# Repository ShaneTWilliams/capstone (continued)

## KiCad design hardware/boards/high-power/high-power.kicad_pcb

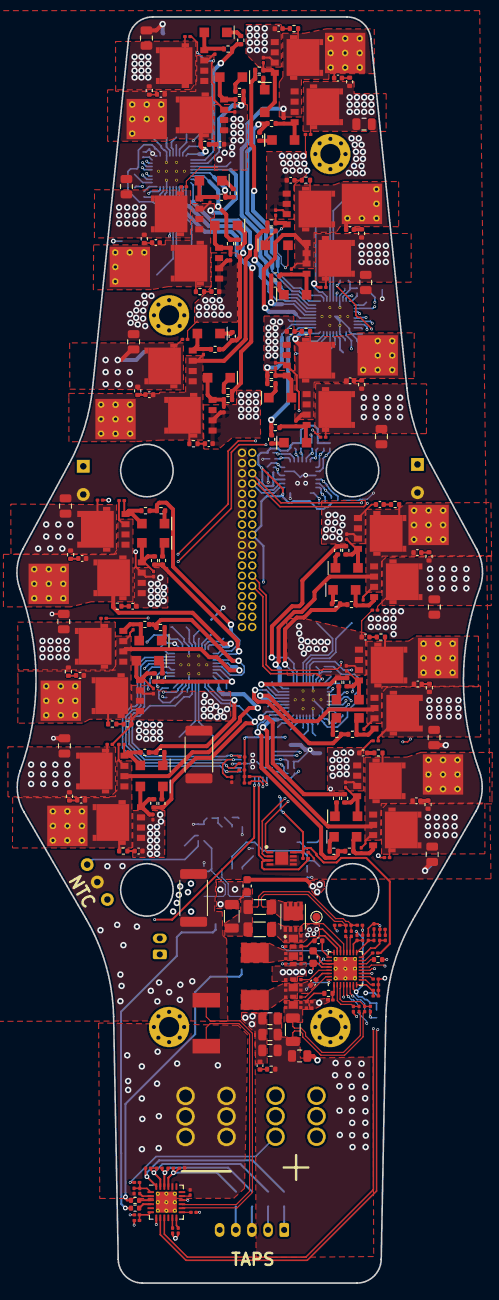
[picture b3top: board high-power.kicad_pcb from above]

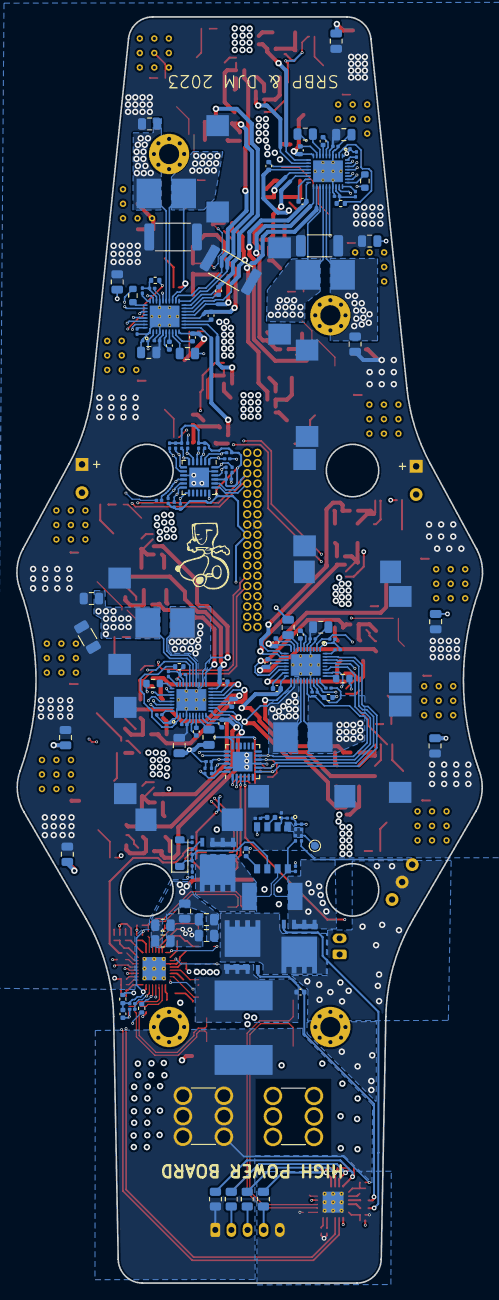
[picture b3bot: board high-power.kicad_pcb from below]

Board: 4 copper layers, 57.7 x 157.0 mm, 435 parts (150 on the bottom side), 262 nets.

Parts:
C201, C208, C209: 0.47uF; C_0201_0603Metric
C202, C425, C427, C428: 0.1uF; C_0201_0603Metric
C203, C204, C205, C206, C210: 0.01uF; C_0201_0603Metric
C207: 0.1uF; C_0402_1005Metric
C401, C413: 1uF; C_0402_1005Metric
C402, C404, C406, C408, C418, C420, C421, C423, C424: 10uF; C_0805_2012Metric
C403: 33pF; C_0201_0603Metric
C405: 1800pF; C_0201_0603Metric
C407: 680pF; C_0201_0603Metric
C409, C412: 33nF; C_0201_0603Metric
C410: 15pF; C_0201_0603Metric
C411: 1nF; C_0201_0603Metric
C414: 10nF; C_0201_0603Metric
C415: 470nF; C_0201_0603Metric
C416, C417: 47nF; C_0402_1005Metric
C419: 3.3uF; C_0603_1608Metric
C422, C426: 100pF; C_0201_0603Metric
C429: 10uF; C_0603_1608Metric
C501, C502, C706, C806, C906, C1006: 0.1u; C_0201_0603Metric
C503: 6.2n; C_0402_1005Metric
C504: 10n; C_0201_0603Metric
C505, C506, C508, C509, C511, C512, C513, C514, C515, C516, C704, C705, C804, C805, C904, C905, C1004, C1005: 10u; C_0805_2012Metric
C507, C510: 220u; CP_Radial_D8.0mm_P3.50mm
C601, C602, C1101: 100n; C_0201_0603Metric
C701, C702, C703, C801, C802, C803, C901, C902, C903, C1001, C1002, C1003: 1u; C_0201_0603Metric
C707, C807, C907, C1007: 470n; C_0402_1005Metric
C708, C709, C710, C808, C809, C810, C908, C909, C910, C1008, C1009, C1010: 1u; C_0402_1005Metric
C711, C712, C715, C716, C719, C720, C811, C812, C815, C816, C819, C820, C911, C912, C915, C916, C919, C920, C1011, C1012, C1015, C1016, C1019, C1020: 3900p; C_0402_1005Metric
C713, C717, C721, C813, C817, C821, C913, C917, C921, C1013, C1017, C1021: 0.01u; C_0201_0603Metric
C714, C718, C722, C814, C818, C822, C914, C918, C922, C1014, C1018, C1022: 4.7u; C_0805_2012Metric
D501: MMSZ5248B; D_SOD-123
D502: SML-P11UTT86R; LED_0402_1005Metric
D701, D702, D703, D704, D705, D706, D801, D802, D803, D804, D805, D806, D901, D902, D903, D904, D905, D906, D1001, D1002, D1003, D1004, D1005, D1006: PMEG4030ER,115; SOD123W
F201: 3-139-122 50A Fuse; 3-139-124
H101, H102, H103, H104: MountingHole; MountingHole_2.5mm_Pad_Via
J101: Conn_02x18_Top_Bottom; 20021311-00036T4LF
J201, J202: Screw_Terminal_01x01; 7461057
J203: Cell Taps; JST_PH_S5B-PH-K_1x05_P2.00mm_Horizontal
J204: 10k NTC Thermistor; JST_PH_S2B-PH-K_1x02_P2.00mm_Horizontal
J601, J701, J801, J901: C; MotorPad
J602, J702, J802, J902: B; MotorPad
J603, J703, J803, J903: A; MotorPad
L401: 2.2u; IHLP2525EZER2R2M01
Q101, Q201, Q202: BSC005N03LS5
Q401, Q402, Q403, Q404: DMN3020UFDF-7
Q405: DMP3013SFV; DMP3013SFV7
Q701, Q702, Q703, Q704, Q705, Q706, Q801, Q802, Q803, Q804, Q805, Q806, Q901, Q902, Q903, Q904, Q905, Q906, Q1001, Q1002, Q1003, Q1004, Q1005, Q1006: NTMFS5C426NT1G
R100, R101, R103, R104: 0; R_2512_6332Metric
R102: 0; R_2010_5025Metric
R105, R107, R108, R109, R110, R111, R112, R113, R114, R115, R116: 0; 5104TR
R106: 0; R_1206_3216Metric
R201, R420, R423: 10R; R_0201_0603Metric
R202, R203, R204: 27R 1/2W; R_0805_2012Metric
R205: 51R 1/2W; R_0805_2012Metric
R206, R211, R507: 1k; R_0201_0603Metric
R207, R504: 1m; EBWM2512F1L00S9
R208, R209: 100R; R_0402_1005Metric
R210, R403, R410, R412, R415, R601, R602, R603, R703, R704, R705, R712, R713, R720, R721, R729, R730, R803, R804, R805, R812, R813, R820, R821, R829, R830, R903, R904, R905, R912, R913, R920, R921, R929, R930, R1003, R1004, R1005, R1012, R1013, R1020, R1021, R1029, R1030, R1101, R1102: 10k; R_0201_0603Metric
R401: 2.2R; R_0402_1005Metric
R402: 40.2k; R_0201_0603Metric
R404, R406: 4.99R; R_0201_0603Metric
R405, R421: 10m; R_1206_3216Metric
R407: 10R; R_0402_1005Metric
R408: 76.8k; R_0201_0603Metric
R409, R417, R502, R508: 100k; R_0201_0603Metric
R411: 1R; R_0402_1005Metric
R413, R414: 0R; R_0402_1005Metric
R416: 30k; R_0201_0603Metric
R418: 300k; R_0201_0603Metric
R419, R424: 0R; R_1206_3216Metric
R422: 137k; R_0201_0603Metric
R501, R506: 100; R_0201_0603Metric
R503, R509: 10.6k; R_0201_0603Metric
R505: 10; R_0201_0603Metric
R510: 13k; R_0201_0603Metric
R701, R702, R801, R802, R901, R902, R1001, R1002: 5.1k; R_0201_0603Metric
R706, R806, R906, R1006: 0; R_0402_1005Metric
R707, R807, R907, R1007: 0R; R_0603_1608Metric
R708, R709, R710, R711, R714, R715, R716, R719, R722, R723, R725, R728, R808, R809, R810, R811, R814, R815, R816, R819, R822, R823, R825, R828, R908, R909, R910, R911, R914, R915, R916, R919, R922, R923, R925, R928, R1008, R1009, R1010, R1011, R1014, R1015, R1016, R1019, R1022, R1023, R1025, R1028: 15; R_0402_1005Metric
R717, R718, R726, R727, R731, R732, R817, R818, R826, R827, R831, R832, R917, R918, R926, R927, R931, R932, R1017, R1018, R1026, R1027, R1031, R1032: 1.50; R_0402_1005Metric
R724, R824, R924, R1024: 2m; PA2512FKF7T0R002E
SW501: SW_SPDT; EG1270
TP407: TestPoint; TestPoint_Pad_D1.0mm
TP501: ON; TestPoint_Pad_D1.0mm
U201: MAX17320G20+T; QFN-24-1EP_4x4mm_P0.5mm_EP2.6x2.6mm_ThermalVias
U401: BQ25703ARSNT; QFN-32-1EP_4x4mm_P0.4mm_EP2.9x2.9mm_ThermalVias
U501: LT1641-1; LT1641-1CS8TRPBF
U601, U1101: TCA9539RTWR; WQFN-24-1EP_4x4mm_P0.5mm_EP2.45x2.45mm
U602: LM75BTP,147
U701, U801, U901, U1001: MCT8329A

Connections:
+3V3: C601.1, C602.1, C1101.1, J101.27, R410.2, R412.1, R415.2, R602.1, R603.1, R701.1, R703.1, R704.1, R801.1, R803.1, R804.1, R901.1, R903.1, R904.1, R1001.1, R1003.1, R1004.1, R1102.1, U601.21 (VCC), U602.8 (VCC), U1101.18 (A0), U1101.21 (VCC)
+BATT: C505.1, C506.1, C507.1, C508.1, C509.1, C510.1, C511.1, C512.1, C513.1, C514.1, C515.1, C516.1, C704.2, C706.2, C713.2, C714.2, C717.2, C718.2, C721.2, C722.2, C804.2, C806.2, C813.2, C814.2, C817.2, C818.2, C821.2, C822.2, C904.2, C906.2, C913.2, C914.2, C917.2, C918.2, C921.2, C922.2, C1004.2, C1006.2, C1013.2, C1014.2, C1017.2, C1018.2, C1021.2, C1022.2, J101.8, Q101.3 (S), Q701.3 (D), Q703.3 (D), Q705.3 (D), Q801.3 (D), Q803.3 (D), Q805.3 (D), Q901.3 (D), Q903.3 (D), Q905.3 (D), Q1001.3 (D), Q1003.3 (D), Q1005.3 (D), R100.1, R100.2, R101.1, R101.2, R102.1, R102.2, R105.1, R105.2, R106.1, R106.2, R107.1, R107.2, R108.1, R108.2, R109.1, R109.2, R110.1, R110.2, R111.1, R111.2, R112.1, R112.2, R113.1, R113.2, R114.1, R114.2, R115.1, R115.2, R116.1, R116.2, R506.2, R508.1, R510.1, R717.1, R726.1, R731.1, R817.1, R826.1, R831.1, R917.1, R926.1, R931.1, R1017.1, R1026.1, R1031.1, U701.5 (PVDD), U801.5 (PVDD), U901.5 (PVDD), U1001.5 (PVDD)
/MTR_FL_CS: J101.19, U701.33 (DACOUT/SOx/SPEED_ANA)
/MTR_FL_SPEED: J101.20, U701.27 (SPEED/WAKE)
/MTR_FR_CS: J101.26, U801.33 (DACOUT/SOx/SPEED_ANA)
/MTR_FR_SPEED: J101.25, U801.27 (SPEED/WAKE)
/MTR_RL_CS_CONN: J101.13, U901.33 (DACOUT/SOx/SPEED_ANA)
/MTR_RL_SPD_CONN: J101.12, U901.27 (SPEED/WAKE)
/MTR_RR_CS: J101.31, U1001.33 (DACOUT/SOx/SPEED_ANA)
/MTR_RR_SPEED: J101.32, U1001.27 (SPEED/WAKE)
/Motors/ESC_FL/BRAKE: R703.2, U601.3 (P02), U701.34 (BRAKE)
/Motors/ESC_FL/DIR: R705.1, U601.1 (P00), U701.31 (DIR)
/Motors/ESC_FL/DRVOFF: R704.2, U601.2 (P01), U701.24 (DRVOFF)
/Motors/ESC_FL/FG: R702.2, U701.28 (FG)
/Motors/ESC_FL/nFAULT: R701.2, U601.4 (P03), U701.35 (nFAULT)
/Motors/ESC_FR/BRAKE: R803.2, U601.7 (P06), U801.34 (BRAKE)
/Motors/ESC_FR/DIR: R805.1, U601.5 (P04), U801.31 (DIR)
/Motors/ESC_FR/DRVOFF: R804.2, U601.6 (P05), U801.24 (DRVOFF)
/Motors/ESC_FR/FG: R802.2, U801.28 (FG)
/Motors/ESC_FR/nFAULT: R801.2, U601.8 (P07), U801.35 (nFAULT)
/Motors/ESC_RL/FG: R902.2, U901.28 (FG)
/Motors/ESC_RL_BRAKE: R903.2, U901.34 (BRAKE), U1101.8 (P07)
/Motors/ESC_RL_DIR: R905.1, U901.31 (DIR), U1101.10
/Motors/ESC_RL_DRVOFF: R904.2, U901.24 (DRVOFF), U1101.11
/Motors/ESC_RL_nFAULT: R901.2, U901.35 (nFAULT), U1101.7 (P06)
/Motors/ESC_RR/BRAKE: R1003.2, U601.12, U1001.34 (BRAKE)
/Motors/ESC_RR/DIR: R1005.1, U601.10, U1001.31 (DIR)
/Motors/ESC_RR/DRVOFF: R1004.2, U601.11, U1001.24 (DRVOFF)
/Motors/ESC_RR/FG: R1002.2, U1001.28 (FG)
/Motors/ESC_RR/nFAULT: R1001.2, U601.13, U1001.35 (nFAULT)
/Motors/~MTR_TMP_OS: R603.2, U602.3 (OS), U1101.3 (P02)
/Power & Charging/BMS/CELL1: J203.4, R205.1
/Power & Charging/BMS/CELL2: J203.3, R204.1
/Power & Charging/BMS/CELL3: J203.2, R203.1
/Power & Charging/BMS/CELL4: F201.1, J202.1, J203.1, R201.1, R202.1
/Power & Charging/BMS_ALRT: U201.7 (ALRT), U1101.4 (P03)
/Power & Charging/CC_CHRG_OK: R412.2, U401.4 (CHRG_OK), U1101.2 (P01)
/Power & Charging/Charge Controller/ILIM_HIZ: R408.2, R409.1, U401.6 (ILIM_HIZ)
/Power & Charging/Charge Controller/REGN: C419.1, R407.1, U401.28 (REGN)
/Power & Charging/Charge Controller/VDDA: C413.1, R407.2, R408.1, R417.1, U401.7 (VDDA)
/Power & Charging/Hotswap/BATT_GOOD: D502.2 (A), R510.2
/Power & Charging/Hotswap/BATT_RAW: C502.1, Q202.3 (S), R211.1, R424.1, R502.1, R504.2, U501.8 (Vcc)
/Power & Charging/Hotswap/SENSE: Q101.1 (D), R504.1, U501.7 (Sense)
/Power & Charging/~CC_PROCHOT: R410.1, U401.11 (~PROCHOT), U1101.1 (P00)
/SCL: J101.22, U201.8 (SCL), U401.13 (SCL), U601.19 (SCL), U602.2 (SCL), U701.30 (SCL), U801.30 (SCL), U901.30 (SCL), U1001.30 (SCL), U1101.19 (SCL)
/SDA: J101.21, R707.1, R807.1, R907.1, R1007.1, U201.9 (SDA), U401.12 (SDA), U601.20 (SDA), U602.1 (SDA), U1101.20 (SDA)
/VBUS: C402.1, C404.1, C406.1, C408.1, J101.14, J101.15, J101.16, J101.17, J101.18, J101.33, J101.34, J101.35, J101.36, R401.1, R404.1, R405.1
/~MTR_IOX_INT: J101.24, R602.2, U601.22 (~INT)
/~MTR_IOX_RST: J101.23, R601.1, U601.24 (~RESET)
/~PWR_IOX_INT: J101.30, R1102.2, U1101.22 (~INT)
/~PWR_IOX_RST: J101.29, R1101.1, U1101.24 (~RESET)
GND: C401.2, C402.2, C403.2, C404.2, C405.2, C406.2, C407.2, C408.2, C409.2, C410.2, C411.2, C412.2, C413.2, C414.2, C415.2, C418.2, C419.2, C420.2, C421.2, C422.2, C423.2, C424.2, C425.1, C426.2, C428.1, C429.2, C501.2, C502.2, C503.2, C504.2, C505.2, C506.2, C507.2, C508.2, C509.2, C510.2, C511.2, C512.2, C513.2, C514.2, C515.2, C516.2, C601.2, C602.2, C701.1, C702.2, C703.1, C704.1, C705.1, C706.1, C714.1, C718.1, C722.1, C801.1, C802.2, C803.1, C804.1, C805.1, C806.1, C814.1, C818.1, C822.1, C901.1, C902.2, C903.1, C904.1, C905.1, C906.1, C914.1, C918.1, C922.1, C1001.1, C1002.2, C1003.1, C1004.1, C1005.1, C1006.1, C1014.1, C1018.1, C1022.1, C1101.2, J101.1, J101.2, J101.3, J101.4, J101.5, J101.6, J101.7, J101.9, J101.10, J101.11, J101.28, Q402.3 (S), Q403.3 (S), R103.1, R103.2, R104.1, R104.2, R207.2, R409.2, R413.2, R414.2, R416.2, R418.2, R422.2, R503.2, R509.2, R601.2, R705.2, R724.2, R805.2, R824.2, R905.2, R924.2, R1005.2, R1024.2, R1101.2, SW501.2 (B), U201.14 (CSN), U401.27 (PGND), U401.33 (THERMAL_PAD), U501.4 (GND), U601.9 (GND), U601.18 (A0), U601.23 (A1), U601.25 (EP), U602.4 (GND), U602.5 (A2), U602.6 (A1), U602.7 (A0), U602.9 (EP), U701.1 (DGND), U701.4 (GND), U701.23 (SN), U701.25 (AGND), U701.37 (PAD), U801.1 (DGND), U801.4 (GND), U801.23 (SN), U801.25 (AGND), U801.37 (PAD), U901.1 (DGND), U901.4 (GND), U901.23 (SN), U901.25 (AGND), U901.37 (PAD), U1001.1 (DGND), U1001.4 (GND), U1001.23 (SN), U1001.25 (AGND), U1001.37 (PAD), U1101.9 (GND), U1101.23 (A1), U1101.25 (EP)
GNDPWR: C202.2, C206.2, C208.2, C209.2, C210.2, J201.1, J203.5, J204.2, R206.1, R207.1, R210.1, U201.15 (CSP), U201.20 (GND), U201.25 (CENTER_PAD)
unnamed: C401.1, R401.2
unnamed: C405.1, R402.2
unnamed: C407.1, R403.2
unnamed: C427.2, C428.2, C429.1, R419.2, R421.2, R423.2, R424.2
unnamed: C504.1, R507.1
unnamed: C711.1, R717.2
unnamed: C712.1, R718.2
unnamed: C715.1, R726.2
unnamed: C716.1, R727.2
unnamed: C719.1, R731.2
unnamed: C720.1, R732.2
unnamed: C811.1, R817.2
unnamed: C812.1, R818.2
unnamed: C815.1, R826.2
unnamed: C816.1, R827.2
unnamed: C819.1, R831.2
unnamed: C820.1, R832.2
unnamed: C911.1, R917.2
unnamed: C912.1, R918.2
unnamed: C915.1, R926.2
unnamed: C916.1, R927.2
unnamed: C919.1, R931.2
unnamed: C920.1, R932.2
unnamed: C1011.1, R1017.2
unnamed: C1012.1, R1018.2
unnamed: C1015.1, R1026.2
unnamed: C1016.1, R1027.2
unnamed: C1019.1, R1031.2
unnamed: C1020.1, R1032.2
unnamed: D501.2 (A), R506.1
unnamed: D501.1 (K), R505.1, R507.2, U501.6 (GATE)
unnamed: D502.1 (K), U501.3 (PWRGD)
unnamed: D701.2 (A), Q702.2 (G), R710.1, R712.2
unnamed: D701.1 (K), R708.1
unnamed: D702.2 (A), Q701.2 (G), R711.1, R713.2
unnamed: D702.1 (K), R709.1
unnamed: D703.2 (A), Q704.2 (G), R715.1, R721.2
unnamed: D703.1 (K), R714.1
unnamed: D704.2 (A), Q703.2 (G), R719.1, R720.2
unnamed: D704.1 (K), R716.1
unnamed: D705.2 (A), Q706.2 (G), R723.1, R730.2
unnamed: D705.1 (K), R722.1
unnamed: D706.2 (A), Q705.2 (G), R728.1, R729.2
unnamed: D706.1 (K), R725.1
unnamed: D801.2 (A), Q802.2 (G), R810.1, R812.2
unnamed: D801.1 (K), R808.1
unnamed: D802.2 (A), Q801.2 (G), R811.1, R813.2
unnamed: D802.1 (K), R809.1
unnamed: D803.2 (A), Q804.2 (G), R815.1, R821.2
unnamed: D803.1 (K), R814.1
unnamed: D804.2 (A), Q803.2 (G), R819.1, R820.2
unnamed: D804.1 (K), R816.1
unnamed: D805.2 (A), Q806.2 (G), R823.1, R830.2
unnamed: D805.1 (K), R822.1
unnamed: D806.2 (A), Q805.2 (G), R828.1, R829.2
unnamed: D806.1 (K), R825.1
unnamed: D901.2 (A), Q902.2 (G), R910.1, R912.2
unnamed: D901.1 (K), R908.1
unnamed: D902.2 (A), Q901.2 (G), R911.1, R913.2
unnamed: D902.1 (K), R909.1
unnamed: D903.2 (A), Q904.2 (G), R915.1, R921.2
unnamed: D903.1 (K), R914.1
unnamed: D904.2 (A), Q903.2 (G), R919.1, R920.2
unnamed: D904.1 (K), R916.1
unnamed: D905.2 (A), Q906.2 (G), R923.1, R930.2
unnamed: D905.1 (K), R922.1
unnamed: D906.2 (A), Q905.2 (G), R928.1, R929.2
unnamed: D906.1 (K), R925.1
unnamed: D1001.2 (A), Q1002.2 (G), R1010.1, R1012.2
unnamed: D1001.1 (K), R1008.1
unnamed: D1002.2 (A), Q1001.2 (G), R1011.1, R1013.2
unnamed: D1002.1 (K), R1009.1
unnamed: D1003.2 (A), Q1004.2 (G), R1015.1, R1021.2
unnamed: D1003.1 (K), R1014.1
unnamed: D1004.2 (A), Q1003.2 (G), R1019.1, R1020.2
unnamed: D1004.1 (K), R1016.1
unnamed: D1005.2 (A), Q1006.2 (G), R1023.1, R1030.2
unnamed: D1005.1 (K), R1022.1
unnamed: D1006.2 (A), Q1005.2 (G), R1028.1, R1029.2
unnamed: D1006.1 (K), R1025.1
unnamed: J204.1, U201.16 (TH2)
unnamed: C710.2, C711.2, J601.1, Q701.1 (S), Q702.3 (D), R713.1, R718.1, U701.18 (SHC)
unnamed: C709.2, C715.2, J602.1, Q703.1 (S), Q704.3 (D), R720.1, R727.1, U701.14 (SHB)
unnamed: C708.2, C719.2, J603.1, Q705.1 (S), Q706.3 (D), R729.1, R732.1, U701.10 (SHA)
unnamed: C810.2, C811.2, J701.1, Q801.1 (S), Q802.3 (D), R813.1, R818.1, U801.18 (SHC)
unnamed: C809.2, C815.2, J702.1, Q803.1 (S), Q804.3 (D), R820.1, R827.1, U801.14 (SHB)
unnamed: C808.2, C819.2, J703.1, Q805.1 (S), Q806.3 (D), R829.1, R832.1, U801.10 (SHA)
unnamed: C910.2, C911.2, J801.1, Q901.1 (S), Q902.3 (D), R913.1, R918.1, U901.18 (SHC)
unnamed: C909.2, C915.2, J802.1, Q903.1 (S), Q904.3 (D), R920.1, R927.1, U901.14 (SHB)
unnamed: C908.2, C919.2, J803.1, Q905.1 (S), Q906.3 (D), R929.1, R932.1, U901.10 (SHA)
unnamed: C1010.2, C1011.2, J901.1, Q1001.1 (S), Q1002.3 (D), R1013.1, R1018.1, U1001.18 (SHC)
unnamed: C1009.2, C1015.2, J902.1, Q1003.1 (S), Q1004.3 (D), R1020.1, R1027.1, U1001.14 (SHB)
unnamed: C1008.2, C1019.2, J903.1, Q1005.1 (S), Q1006.3 (D), R1029.1, R1032.1, U1001.10 (SHA)
unnamed: Q101.2 (G), R505.2
unnamed: Q201.1 (D), Q202.1 (D)
unnamed: C207.2, Q201.2 (G), R208.1
unnamed: C207.1, F201.2, Q201.3 (S)
unnamed: Q202.2 (G), R209.1
unnamed: C411.1, C414.1, Q401.1 (D), R405.2, R406.1, R411.1
unnamed: Q401.2 (G), U401.31 (HIDRV1)
unnamed: C416.1, L401.1, Q401.3 (S), Q402.1 (D), U401.32 (SW1)
unnamed: Q402.2 (G), U401.29 (LODRV1)
unnamed: C417.1, L401.2, Q403.1 (D), Q404.3 (S), U401.23 (SW2)
unnamed: Q403.2 (G), U401.26 (LODRV2)
unnamed: C418.1, C420.1, C421.1, C423.1, C424.1, Q404.1 (D), Q405.3 (S), R419.1, U401.22 (VSYS)
unnamed: Q404.2 (G), U401.24 (HIDRV2)
unnamed: C425.2, C427.1, Q405.1 (D), R420.2, R421.1
unnamed: Q405.2 (G), TP407.1, U401.21 (~BATDRV)
unnamed: C712.2, C713.1, C716.2, C717.1, C720.2, C721.1, Q702.1 (S), Q704.1 (S), Q706.1 (S), R712.1, R721.1, R724.1, R730.1, U701.21 (LSS), U701.22 (SP)
unnamed: C812.2, C813.1, C816.2, C817.1, C820.2, C821.1, Q802.1 (S), Q804.1 (S), Q806.1 (S), R812.1, R821.1, R824.1, R830.1, U801.21 (LSS), U801.22 (SP)
unnamed: C912.2, C913.1, C916.2, C917.1, C920.2, C921.1, Q902.1 (S), Q904.1 (S), Q906.1 (S), R912.1, R921.1, R924.1, R930.1, U901.21 (LSS), U901.22 (SP)
unnamed: C1012.2, C1013.1, C1016.2, C1017.1, C1020.2, C1021.1, Q1002.1 (S), Q1004.1 (S), Q1006.1 (S), R1012.1, R1021.1, R1024.1, R1030.1, U1001.21 (LSS), U1001.22 (SP)
unnamed: R501.2, SW501.3 (C)
unnamed: R210.2, U201.12 (AOLDO)
unnamed: C203.1, R202.2, U201.24 (BATTS)
unnamed: C205.2, C206.1, R205.2, U201.21 (CELL1)
unnamed: C204.2, C205.1, R204.2, U201.22 (CELL2)
unnamed: C203.2, C204.1, R203.2, U201.23 (CELL3)
unnamed: R208.2, U201.3 (CHG)
unnamed: C201.1, U201.2 (CP)
unnamed: R209.2, U201.4 (DIS)
unnamed: C201.2, C202.1, R201.2, U201.1 (IN)
unnamed: C210.1, R211.2, U201.6 (PCKP)
unnamed: R206.2, U201.11 (PFAIL)
unnamed: C208.1, U201.17 (REG2)
unnamed: C209.1, U201.13 (REG3)
unnamed: C412.1, R406.2, U401.2 (ACN)
unnamed: C409.1, R404.2, U401.3 (ACP)
unnamed: C416.2, U401.30 (BTST1)
unnamed: C417.2, U401.25 (BTST2)
unnamed: R417.2, R418.1, U401.18 (CELL_BATPRESZ)
unnamed: R414.1, U401.14 (CMPIN)
unnamed: R415.1, U401.15 (CMPOUT)
unnamed: C403.1, R402.1, U401.16 (COMP1)
unnamed: C410.1, R403.1, U401.17 (COMP2)
unnamed: R413.1, U401.5 (EN_OTG)
unnamed: C426.1, R422.1, U401.8 (IADPT)
unnamed: C422.1, U401.9 (IBAT)
unnamed: R416.1, U401.10 (PSYS)
unnamed: R423.1, U401.19 (SRN)
unnamed: R420.1, U401.20 (SRP)
unnamed: C415.1, R411.2, U401.1 (VBUS)
unnamed: R508.2, R509.1, U501.2 (FB)
unnamed: C501.1, R501.1, R502.2, R503.1, TP501.1, U501.1 (ON)
unnamed: C503.1, U501.5 (TIMER)
unnamed: C701.2, R702.1, R706.1, U701.26 (AVDD)
unnamed: C708.1, U701.9 (BSTA)
unnamed: C709.1, U701.13 (BSTB)
unnamed: C710.1, U701.17 (BSTC)
unnamed: C707.1, U701.7 (CPH)
unnamed: C707.2, U701.6 (CPL)
unnamed: C703.2, U701.36 (DVDD)
unnamed: R725.2, R728.2, U701.11 (GHA)
unnamed: R716.2, R719.2, U701.15 (GHB)
unnamed: R709.2, R711.2, U701.19 (GHC)
unnamed: R722.2, R723.2, U701.12 (GLA)
unnamed: R714.2, R715.2, U701.16 (GLB)
unnamed: R708.2, R710.2, U701.20 (GLC)
unnamed: C705.2, U701.8 (GVDD)
unnamed: R707.2, U701.29 (SDA)
unnamed: C702.1, R706.2, U701.2 (VREG)
unnamed: C801.2, R802.1, R806.1, U801.26 (AVDD)
unnamed: C808.1, U801.9 (BSTA)
unnamed: C809.1, U801.13 (BSTB)
unnamed: C810.1, U801.17 (BSTC)
unnamed: C807.1, U801.7 (CPH)
unnamed: C807.2, U801.6 (CPL)
unnamed: C803.2, U801.36 (DVDD)
unnamed: R825.2, R828.2, U801.11 (GHA)
unnamed: R816.2, R819.2, U801.15 (GHB)
unnamed: R809.2, R811.2, U801.19 (GHC)
unnamed: R822.2, R823.2, U801.12 (GLA)
unnamed: R814.2, R815.2, U801.16 (GLB)
unnamed: R808.2, R810.2, U801.20 (GLC)
unnamed: C805.2, U801.8 (GVDD)
unnamed: R807.2, U801.29 (SDA)
unnamed: C802.1, R806.2, U801.2 (VREG)
unnamed: C901.2, R902.1, R906.1, U901.26 (AVDD)
unnamed: C908.1, U901.9 (BSTA)
unnamed: C909.1, U901.13 (BSTB)
unnamed: C910.1, U901.17 (BSTC)
unnamed: C907.1, U901.7 (CPH)
unnamed: C907.2, U901.6 (CPL)
unnamed: C903.2, U901.36 (DVDD)
unnamed: R925.2, R928.2, U901.11 (GHA)
unnamed: R916.2, R919.2, U901.15 (GHB)
unnamed: R909.2, R911.2, U901.19 (GHC)
unnamed: R922.2, R923.2, U901.12 (GLA)
unnamed: R914.2, R915.2, U901.16 (GLB)
unnamed: R908.2, R910.2, U901.20 (GLC)
unnamed: C905.2, U901.8 (GVDD)
unnamed: R907.2, U901.29 (SDA)
unnamed: C902.1, R906.2, U901.2 (VREG)
unnamed: C1001.2, R1002.1, R1006.1, U1001.26 (AVDD)
unnamed: C1008.1, U1001.9 (BSTA)
unnamed: C1009.1, U1001.13 (BSTB)
unnamed: C1010.1, U1001.17 (BSTC)
unnamed: C1007.1, U1001.7 (CPH)
unnamed: C1007.2, U1001.6 (CPL)
unnamed: C1003.2, U1001.36 (DVDD)
unnamed: R1025.2, R1028.2, U1001.11 (GHA)
unnamed: R1016.2, R1019.2, U1001.15 (GHB)
unnamed: R1009.2, R1011.2, U1001.19 (GHC)
unnamed: R1022.2, R1023.2, U1001.12 (GLA)
unnamed: R1014.2, R1015.2, U1001.16 (GLB)
unnamed: R1008.2, R1010.2, U1001.20 (GLC)
unnamed: C1005.2, U1001.8 (GVDD)
unnamed: R1007.2, U1001.29 (SDA)
unnamed: C1002.1, R1006.2, U1001.2 (VREG)

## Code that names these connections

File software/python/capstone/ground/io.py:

from enum import IntEnum
import time

import RPi.GPIO as gpio_lib
from spidev import SpiDev

from capstone.drivers.sx1262 import *

class CapstonePin(IntEnum):
    # SX1262
    DIGITAL_RADIO_DIO1 = 4
    DIGITAL_RADIO_DIO3 = 5
    DIGITAL_RADIO_BUSY = 6
    DIGITAL_RADIO_RESET = 7
    DIGITAL_RADIO_nCS = 8
    DIGITAL_RADIO_MISO = 9
    DIGITAL_RADIO_MOSI = 10
    DIGITAL_RADIO_SCLK = 11

    # GPS-01
    GPS_UART_RX = 14
    GPS_UART_TX = 15
    GPS_RESET = 16

    # ADV7282A-M
    DIGITIZER_INTRQ = 13
    DIGITIZER_PWRDWN = 22
    DIGITIZER_RESET = 23

    # RX5808
    VIDEO_CH1 = 25
    VIDEO_CH2 = 26
    VIDEO_CH3 = 27

_GPIO_CONFIGS = {
    CapstonePin.DIGITAL_RADIO_DIO1: {
        "mode": gpio_lib.IN
    },
    CapstonePin.DIGITAL_RADIO_DIO3: {
        "mode": gpio_lib.IN
    },
    CapstonePin.DIGITAL_RADIO_BUSY: {
        "mode": gpio_lib.IN
    },
    CapstonePin.DIGITAL_RADIO_RESET: {
        "mode": gpio_lib.OUT,
        "default": gpio_lib.HIGH
    },

    CapstonePin.GPS_RESET: {
        "mode": gpio_lib.OUT,
        "default": gpio_lib.HIGH
    },

    CapstonePin.DIGITIZER_INTRQ: {
        "mode": gpio_lib.IN
    },
    CapstonePin.DIGITIZER_PWRDWN: {
        "mode": gpio_lib.IN
    },
    CapstonePin.DIGITIZER_RESET: {
        "mode": gpio_lib.IN
    },

    CapstonePin.VIDEO_CH1: {
        "mode": gpio_lib.OUT,
        "default": gpio_lib.LOW
    },
    CapstonePin.VIDEO_CH2: {
        "mode": gpio_lib.OUT,
        "default": gpio_lib.LOW
    },
    CapstonePin.VIDEO_CH3: {
        "mode": gpio_lib.OUT,
        "default": gpio_lib.LOW
    },
}

gpio_lib.setmode(gpio_lib.BCM)
gpio_lib.setwarnings(False)

for io, cfg in _GPIO_CONFIGS.items():
    gpio_lib.setup(io, cfg["mode"])
    if cfg["mode"] == gpio_lib.OUT:
        gpio_lib.output(io, cfg["default"])


class CapstoneGPIO:
    def __init__(self, pin):
        self.pin = pin

    def set(self, state):
        if _GPIO_CONFIGS[self.pin]["mode"] != gpio_lib.OUT:
            raise RuntimeException("Can't set input pin state")
        gpio_lib.output(self.pin, state)

    def get(self):
        return bool(gpio_lib.input(self.pin))


class CapstoneSPI:
    SPI_DEVICE = 0
    SPI_BUS = 0
    SPI_SPEED_HZ = 1_000_000
    SPI_MODE = 0b00

    def __init__(self):
        self.bus = SpiDev()
        self.bus.open(self.SPI_BUS, self.SPI_DEVICE)
        self.bus.max_speed_hz = self.SPI_SPEED_HZ
        self.bus.mode = self.SPI_MODE

    def __del__(self):
        self.bus.close()

    def xfer(self, data):
        return self.bus.xfer(data)

GPS_UART_DEV = "/dev/ttyAMA0"
GPS_UART_BAUD = 9600

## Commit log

2023-05-22 Hardware revision 1
2023-05-24 Add MCU flash and USB-PD
2023-05-24 Add first revision of I2C generator
2023-05-24 Add firmware clang-format file
2023-05-26 Add MCT8329A register map
2023-05-26 Change register "address" to "offset" in generate.py
2023-06-28 Add Shane + Dylan's first draft schematics
2023-07-05 Added Power & Charging Subsystems
    - Replaced Qi receiver
    - Added charge controller
    - Added BMS
    - Added switch between Qi & USB-PD
2023-07-06 temp
2023-07-07 Split drone into LP & HP boards
2023-07-09 Add footprints and models for LP board
    Also completed rough layout for LP board to estimate board space usage.
2023-07-12 Add initial changes after schematic review
2023-08-22 Add firmware tools and boilerplate - Bootloader source code - Example application source code - Linker scripts - Firmware build system - Change driver definition files from JSON to YAML - Update driv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
2023-08-23 Fix several driver generator bugs
2023-08-23 Add TCA9539 driver
2023-10-11 Add drone PCB models
    Co-authored by: Stefan Boon-Petersen <sboonpetersen@mun.ca>
2023-10-11 Add drone PCB footprints
    Co-authored by: Stefan Boon-Petersen <sboonpetersen@mun.ca>
2023-10-11 Add drone PCB symbols
    Co-authored by: Stefan Boon-Petersen <sboonpetersen@mun.ca>
2023-10-12 Add low power PCB
    Co-authored by: Stefan Boon-Petersen <sboonpetersen@mun.ca>
2023-10-12 Add high power PCB
    Co-authored by: Stefan Boon-Petersen <sboonpetersen@mun.ca>
2023-10-14 fixup! Add low power PCB
2023-10-14 fixup! Add high power PCB
2023-10-21 Initial ground station commit
2023-10-22 Added power supplies to digitizer IC
2023-10-24 Added oscillator to video digitizer
2023-10-25 Pre-arrival firmware/software changes
2023-11-08 transmitter tx stuff
2023-11-08 Updated video radio to RX5808
2023-12-30 Transmitting power (without wires) (wire delete)
2024-01-08 Change board input power to 5V, add connector for OTS wireless power TX
2024-01-08 Add TVS diode on 5V rail
2024-01-17 sch review
2024-01-18 Added footprints for most things
2024-01-19 Added a couple more footprints, changed TVS diode to uni-directional
2024-01-20 Added footprint for RX5808... This footprint should be reviewed
2024-01-21 Did initial layout. Still need to connect everything together
2024-01-21 Removed 10 pin radio header and changed ribbon cable connector
    - disconnected 3V3 from the ribbon cable connector to keep the Pi 3V3 rail separate from the board 3V3 rail
2024-01-21 layout
2024-01-22 Finished initial layout
2024-01-24 Added voltage divider to RF switch VTCL pin to keep voltage to 1.8V. Adjusted cap size to keep RC cutoff frequency consistent
2024-01-28 base station layout review
2024-01-28 Added silkscreen
2024-01-28 pair length match fix
2024-01-29 Moved a couple components around and added some ground stitching vias
2024-02-06 Generated gerbers
2024-02-08 Board bringup + initial desktop app
2024-03-04 Add base station hardware files
2024-04-02 Final FW/SW work
2024-04-02 Clean up old files
2024-04-30 Touch-ups for ECE faculty demo
